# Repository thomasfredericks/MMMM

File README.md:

# MMMM
MMMM: Mini Mono Matrix Mixer

More information: http://www.tofstuff.com/MMMM

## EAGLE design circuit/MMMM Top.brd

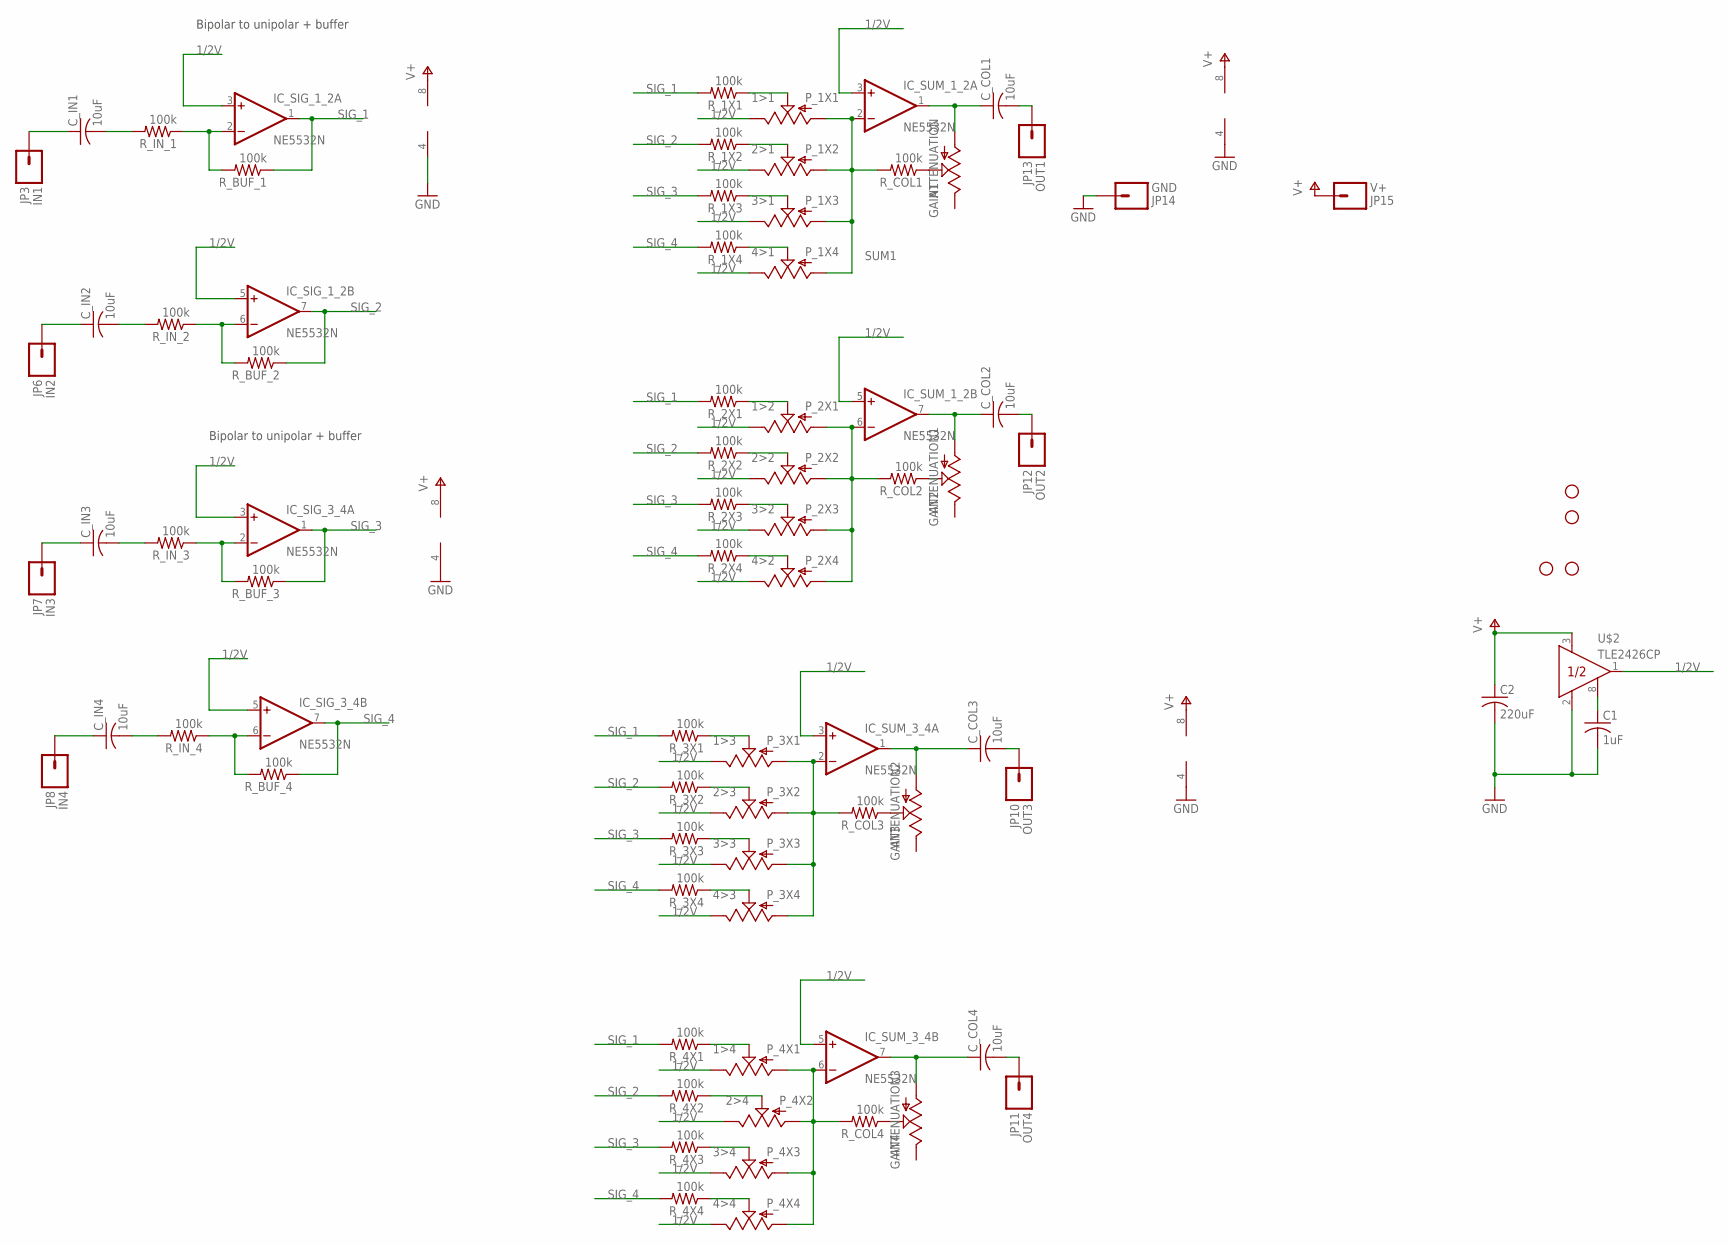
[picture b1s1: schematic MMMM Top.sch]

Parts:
ATTENUATION: GAIN1; TRIM_POT
ATTENUATION1: GAIN2; TRIM_POT
ATTENUATION2: GAIN3; TRIM_POT
ATTENUATION3: GAIN4; TRIM_POT
C1: 1uF; C025-030X050
C2: 220uF; C050-075X075
C_COL1, C_COL2, C_COL3, C_COL4: 10uF; C025-025X050
C_IN1, C_IN2, C_IN3, C_IN4: 10uF; C025-025X050
IC_SIG_1_2, IC_SIG_3_4: NE5532N; DIL08
IC_SUM_1_2, IC_SUM_3_4: NE5532N; DIL08
JP1, JP2, JP4, JP5: STAND-OFF
JP3: IN1; 1X01_SIDE_NAME
JP6: IN2; 1X01_SIDE_NAME
JP7: IN3; 1X01_SIDE_NAME
JP8: IN4; 1X01_SIDE_NAME
JP10: OUT3; 1X01_SIDE_NAME
JP11: OUT4; 1X01_SIDE_NAME
JP12: OUT2; 1X01_SIDE_NAME
JP13: OUT1; 1X01_SIDE_NAME
JP14: GND; 1X01_SIDE_NAME
JP15: V+; 1X01_SIDE_NAME
P_1X1: 1>1; ALPS_POT
P_1X2: 2>1; ALPS_POT
P_1X3: 3>1; ALPS_POT
P_1X4: 4>1; ALPS_POT
P_2X1: 1>2; ALPS_POT
P_2X2: 2>2; ALPS_POT
P_2X3: 3>2; ALPS_POT
P_2X4: 4>2; ALPS_POT
P_3X1: 1>3; ALPS_POT
P_3X2: 2>3; ALPS_POT
P_3X3: 3>3; ALPS_POT
P_3X4: 4>3; ALPS_POT
P_4X1: 1>4; ALPS_POT
P_4X2: 2>4; ALPS_POT
P_4X3: 3>4; ALPS_POT
P_4X4: 4>4; ALPS_POT
R_1X1, R_1X2, R_1X3, R_1X4, R_2X1, R_2X2, R_2X3, R_2X4, R_3X1, R_3X2, R_3X3, R_3X4, R_4X1, R_4X2, R_4X3, R_4X4: 100k; 0204/5
R_BUF_1, R_BUF_2, R_BUF_3, R_BUF_4: 100k; 0204/5
R_COL1, R_COL2, R_COL3, R_COL4: 100k; 0204/5
R_IN_1, R_IN_2, R_IN_3, R_IN_4: 100k; 0204/5
U$2: TLE2426CP; DIP-8

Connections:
1/2V: IC_SIG_1_2.3 (+IN), IC_SIG_1_2.5 (+IN), IC_SIG_3_4.3 (+IN), IC_SIG_3_4.5 (+IN), IC_SUM_1_2.3 (+IN), IC_SUM_1_2.5 (+IN), IC_SUM_3_4.3 (+IN), IC_SUM_3_4.5 (+IN), P_1X1.P$1 (E), P_1X2.P$1 (E), P_1X3.P$1 (E), P_1X4.P$1 (E), P_2X1.P$1 (E), P_2X2.P$1 (E), P_2X3.P$1 (E), P_2X4.P$1 (E), P_3X1.P$1 (E), P_3X2.P$1 (E), P_3X3.P$1 (E), P_3X4.P$1 (E), P_4X1.P$1 (E), P_4X2.P$1 (E), P_4X3.P$1 (E), P_4X4.P$1 (E), U$2.1 (OUT)
GND: C1.2, C2.2, IC_SIG_1_2.4 (V-), IC_SIG_3_4.4 (V-), IC_SUM_1_2.4 (V-), IC_SUM_3_4.4 (V-), JP14.1, U$2.2 (COM)
IN1: C_IN1.1, JP3.1
unnamed: ATTENUATION.1 (S), R_COL1.1
unnamed: IC_SIG_1_2.2 (-IN), R_BUF_1.2, R_IN_1.1
unnamed: C_COL1.2, JP13.1
unnamed: P_2X1.P$2 (S), R_2X1.1
unnamed: ATTENUATION1.1 (S), R_COL2.1
unnamed: C_IN1.2, R_IN_1.2
unnamed: IC_SIG_1_2.6 (-IN), R_BUF_2.2, R_IN_2.1
unnamed: C_IN2.2, R_IN_2.2
unnamed: C_IN2.1, JP6.1
unnamed: P_1X1.P$2 (S), R_1X1.1
unnamed: C1.1, U$2.8 (NR)
unnamed: IC_SIG_3_4.2 (-IN), R_BUF_3.2, R_IN_3.1
unnamed: C_IN3.2, R_IN_3.2
unnamed: C_IN3.1, JP7.1
unnamed: IC_SIG_3_4.6 (-IN), R_BUF_4.2, R_IN_4.1
unnamed: C_IN4.2, R_IN_4.2
unnamed: C_IN4.1, JP8.1
unnamed: ATTENUATION1.3 (A), C_COL2.1, IC_SUM_1_2.7 (OUT)
unnamed: P_1X3.P$2 (S), R_1X3.1
unnamed: P_1X4.P$2 (S), R_1X4.1
unnamed: ATTENUATION.3 (A), C_COL1.1, IC_SUM_1_2.1 (OUT)
unnamed: ATTENUATION2.1 (S), R_COL3.1
unnamed: ATTENUATION3.1 (S), R_COL4.1
unnamed: P_1X2.P$2 (S), R_1X2.1
unnamed: P_2X2.P$2 (S), R_2X2.1
unnamed: C_COL2.2, JP12.1
unnamed: P_2X3.P$2 (S), R_2X3.1
unnamed: IC_SUM_1_2.6 (-IN), P_2X1.P$3 (A), P_2X2.P$3 (A), P_2X3.P$3 (A), P_2X4.P$3 (A), R_COL2.2
unnamed: P_2X4.P$2 (S), R_2X4.1
unnamed: P_3X1.P$2 (S), R_3X1.1
unnamed: ATTENUATION2.3 (A), C_COL3.1, IC_SUM_3_4.1 (OUT)
unnamed: P_3X2.P$2 (S), R_3X2.1
unnamed: C_COL3.2, JP10.1
unnamed: P_3X3.P$2 (S), R_3X3.1
unnamed: IC_SUM_3_4.2 (-IN), P_3X1.P$3 (A), P_3X2.P$3 (A), P_3X3.P$3 (A), P_3X4.P$3 (A), R_COL3.2
unnamed: P_3X4.P$2 (S), R_3X4.1
unnamed: P_4X1.P$2 (S), R_4X1.1
unnamed: ATTENUATION3.3 (A), C_COL4.1, IC_SUM_3_4.7 (OUT)
unnamed: P_4X2.P$2 (S), R_4X2.1
unnamed: C_COL4.2, JP11.1
unnamed: P_4X3.P$2 (S), R_4X3.1
unnamed: IC_SUM_3_4.6 (-IN), P_4X1.P$3 (A), P_4X2.P$3 (A), P_4X3.P$3 (A), P_4X4.P$3 (A), R_COL4.2
unnamed: P_4X4.P$2 (S), R_4X4.1
SIG_1: IC_SIG_1_2.1 (OUT), R_1X1.2, R_2X1.2, R_3X1.2, R_4X1.2, R_BUF_1.1
SIG_2: IC_SIG_1_2.7 (OUT), R_1X2.2, R_2X2.2, R_3X2.2, R_4X2.2, R_BUF_2.1
SIG_3: IC_SIG_3_4.1 (OUT), R_1X3.2, R_2X3.2, R_3X3.2, R_4X3.2, R_BUF_3.1
SIG_4: IC_SIG_3_4.7 (OUT), R_1X4.2, R_2X4.2, R_3X4.2, R_4X4.2, R_BUF_4.1
SUM1: IC_SUM_1_2.2 (-IN), P_1X1.P$3 (A), P_1X2.P$3 (A), P_1X3.P$3 (A), P_1X4.P$3 (A), R_COL1.2
V+: C2.1, IC_SIG_1_2.8 (V+), IC_SIG_3_4.8 (V+), IC_SUM_1_2.8 (V+), IC_SUM_3_4.8 (V+), JP15.1, U$2.3 (IN)

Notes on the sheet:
Bipolar to unipolar + buffer

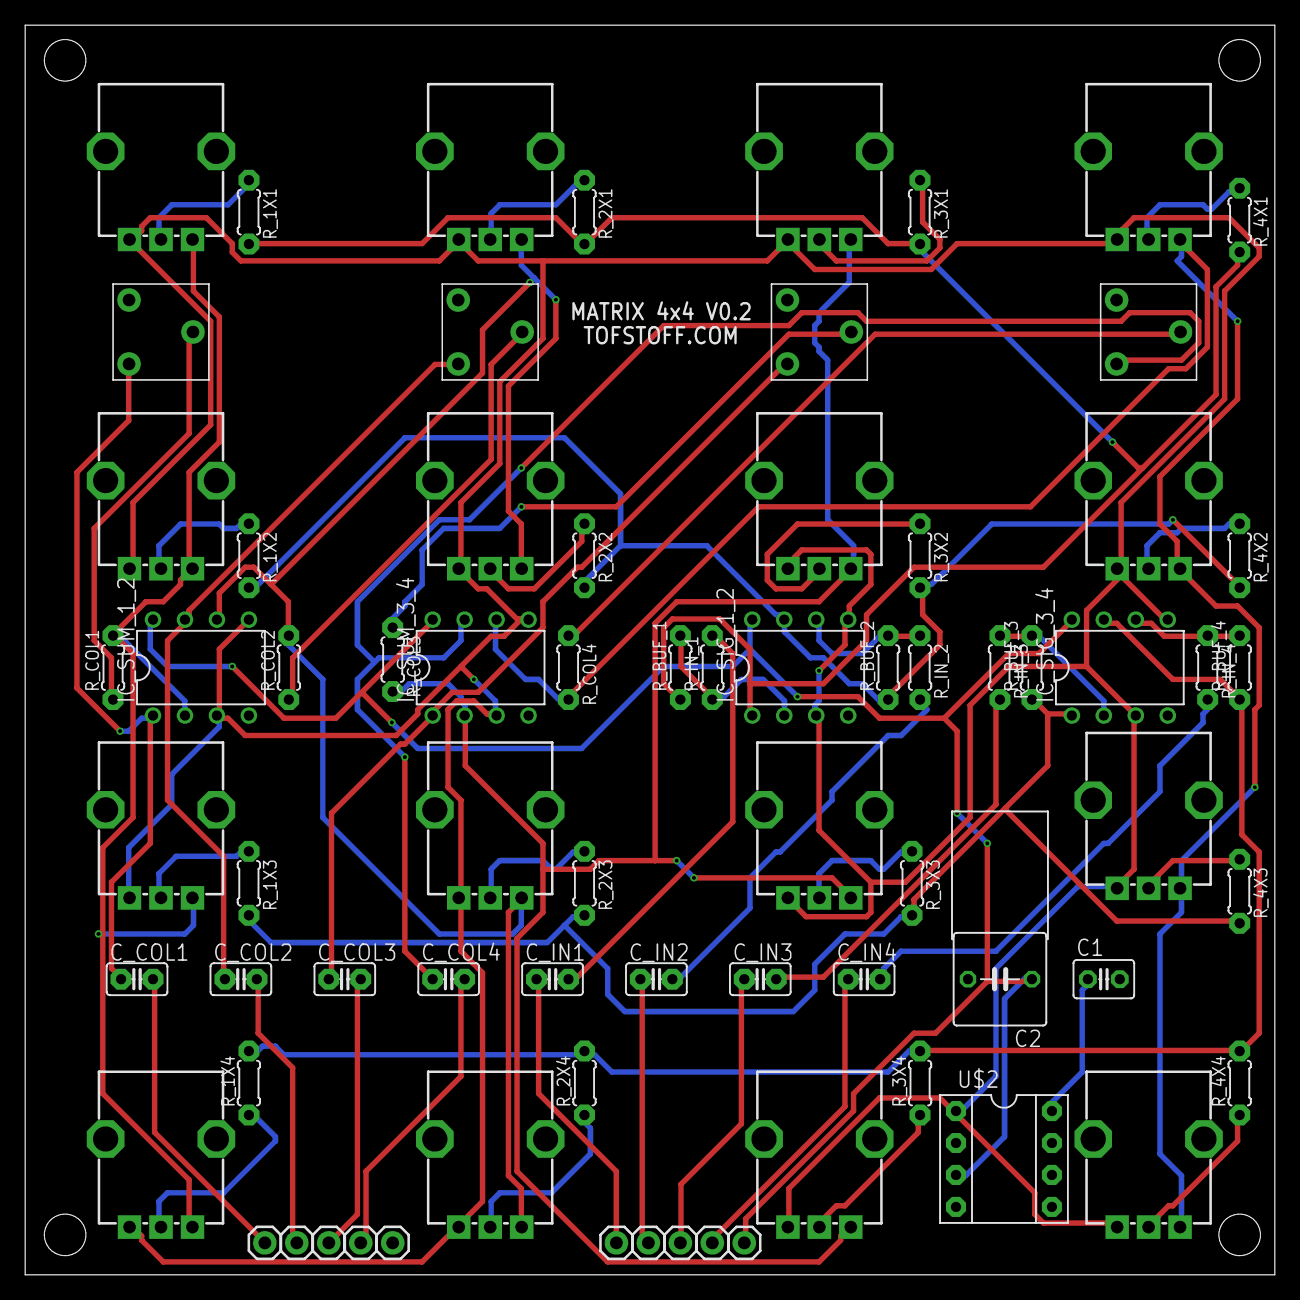
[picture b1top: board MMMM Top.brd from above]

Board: 2 copper layers, 99.3 x 99.3 mm, 77 parts (0 on the bottom side), 52 nets.

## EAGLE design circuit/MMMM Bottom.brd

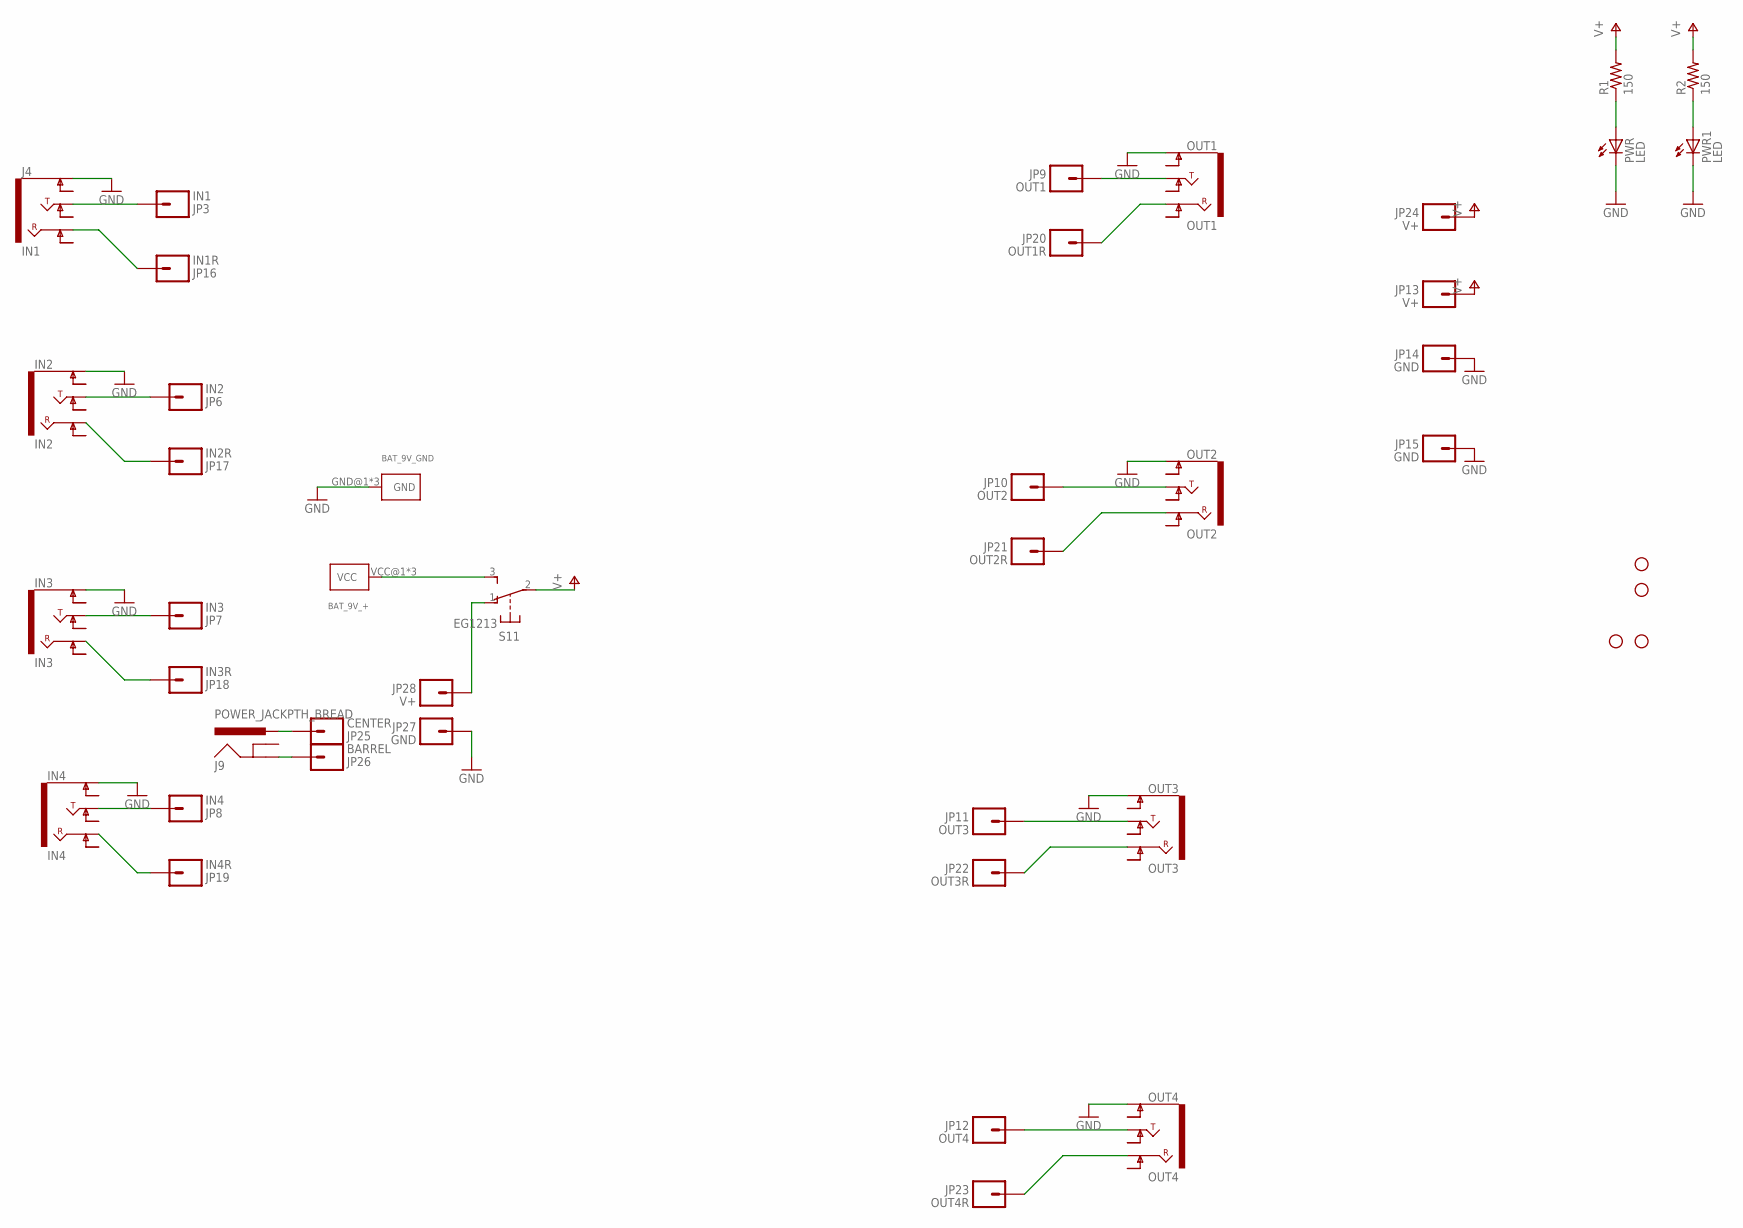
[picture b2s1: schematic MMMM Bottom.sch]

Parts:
BAT_9V_+: KEYSTONE-637; KEYSTONE_AA_AAA_BATTERY_TERMINAL-637
BAT_9V_GND: KEYSTONE-629; KEYSTONE_AA_AAA_BATTERY_TERMINAL-629
IN2: IN2; AUDIO-JACK-.25-INCH-HORIZ-PTH
IN3: IN3; AUDIO-JACK-.25-INCH-HORIZ-PTH
IN4: IN4; AUDIO-JACK-.25-INCH-HORIZ-PTH
J4: IN1; AUDIO-JACK-.25-INCH-HORIZ-PTH
J9: POWER_JACKPTH_BREAD; POWER_JACK_PTH_BREAD
JP1, JP2, JP4, JP5: STAND-OFF
JP3: IN1; 1X01_SIDE_NAME
JP6: IN2; 1X01_SIDE_NAME
JP7: IN3; 1X01_SIDE_NAME
JP8: IN4; 1X01_SIDE_NAME
JP9: OUT1; 1X01_SIDE_NAME
JP10: OUT2; 1X01_SIDE_NAME
JP11: OUT3; 1X01_SIDE_NAME
JP12: OUT4; 1X01_SIDE_NAME
JP13, JP24: V+; 1X01_SIDE_NAME
JP14, JP15: GND; 1X01_SIDE_NAME
JP16: IN1R; 1X01_SIDE_NAME
JP17: IN2R; 1X01_SIDE_NAME
JP18: IN3R; 1X01_SIDE_NAME
JP19: IN4R; 1X01_SIDE_NAME
JP20: OUT1R; 1X01_SIDE_NAME
JP21: OUT2R; 1X01_SIDE_NAME
JP22: OUT3R; 1X01_SIDE_NAME
JP23: OUT4R; 1X01_SIDE_NAME
JP25: CENTER; 1X01_SIDE_NAME_SML
JP26: BARREL; 1X01_SIDE_NAME_SML
JP27: GND; 1X01_SIDE_NAME_SML
JP28: V+; 1X01_SIDE_NAME_SML
OUT1: OUT1; AUDIO-JACK-.25-INCH-HORIZ-PTH
OUT2: OUT2; AUDIO-JACK-.25-INCH-HORIZ-PTH
OUT3: OUT3; AUDIO-JACK-.25-INCH-HORIZ-PTH
OUT4: OUT4; AUDIO-JACK-.25-INCH-HORIZ-PTH
PWR, PWR1: LED; LED3MM-MINUS
R1, R2: 150; 0204/5
S1: EG1213

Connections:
GND: BAT_9V_GND.GND@1, BAT_9V_GND.GND@2, BAT_9V_GND.GND@3, IN2.SLEEVE (EARTH), IN3.SLEEVE (EARTH), IN4.SLEEVE (EARTH), J4.SLEEVE (EARTH), JP14.1, JP15.1, JP27.1, OUT1.SLEEVE (EARTH), OUT2.SLEEVE (EARTH), OUT3.SLEEVE (EARTH), OUT4.SLEEVE (EARTH), PWR.K (C), PWR1.K (C)
unnamed: PWR.A, R1.1
unnamed: IN2.TIP, JP6.1
unnamed: JP9.1, OUT1.TIP
unnamed: IN3.TIP, JP7.1
unnamed: J4.TIP, JP3.1
unnamed: IN4.TIP, JP8.1
unnamed: J4.RING, JP16.1
unnamed: IN3.RING, JP18.1
unnamed: IN4.RING, JP19.1
unnamed: IN2.RING, JP17.1
unnamed: JP20.1, OUT1.RING
unnamed: JP23.1, OUT4.RING
unnamed: JP22.1, OUT3.RING
unnamed: JP21.1, OUT2.RING
unnamed: JP28.1, S1.1 (O)
unnamed: BAT_9V_+.VCC@1, BAT_9V_+.VCC@2, BAT_9V_+.VCC@3, S1.3 (S)
unnamed: PWR1.A, R2.1
unnamed: J9.PWR, JP25.1
unnamed: J9.GND, JP26.1
unnamed: JP10.1, OUT2.TIP
unnamed: JP11.1, OUT3.TIP
unnamed: JP12.1, OUT4.TIP
V+: JP13.1, JP24.1, R1.2, R2.2, S1.2

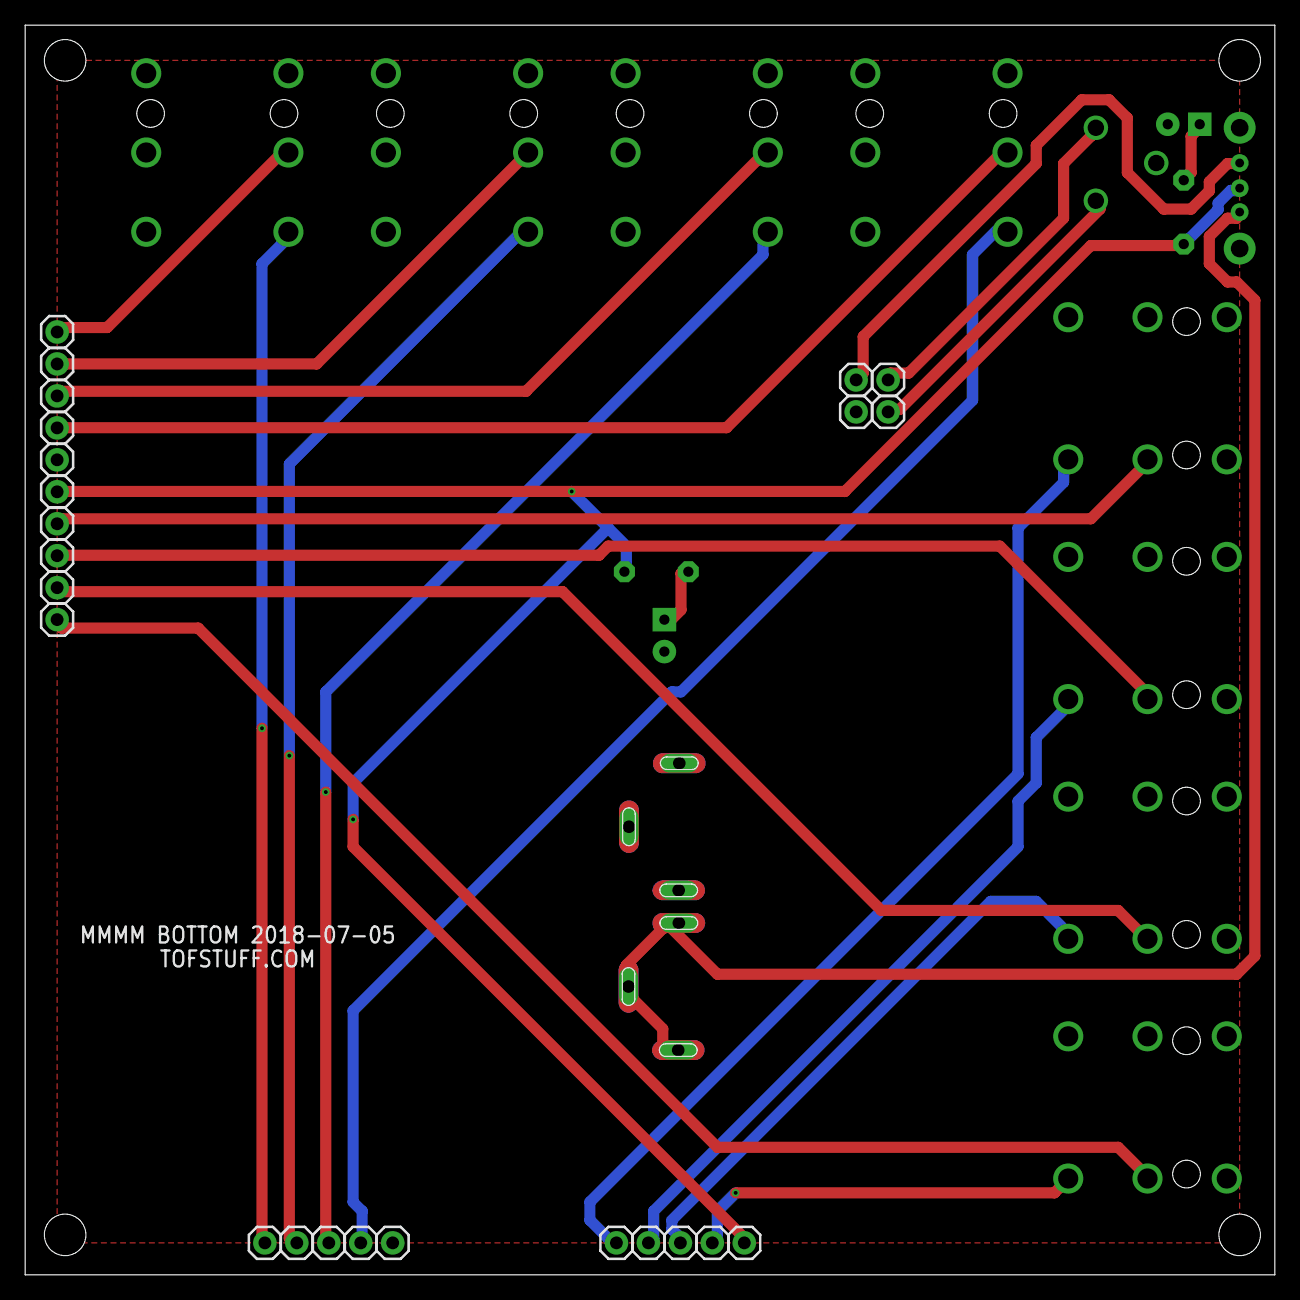
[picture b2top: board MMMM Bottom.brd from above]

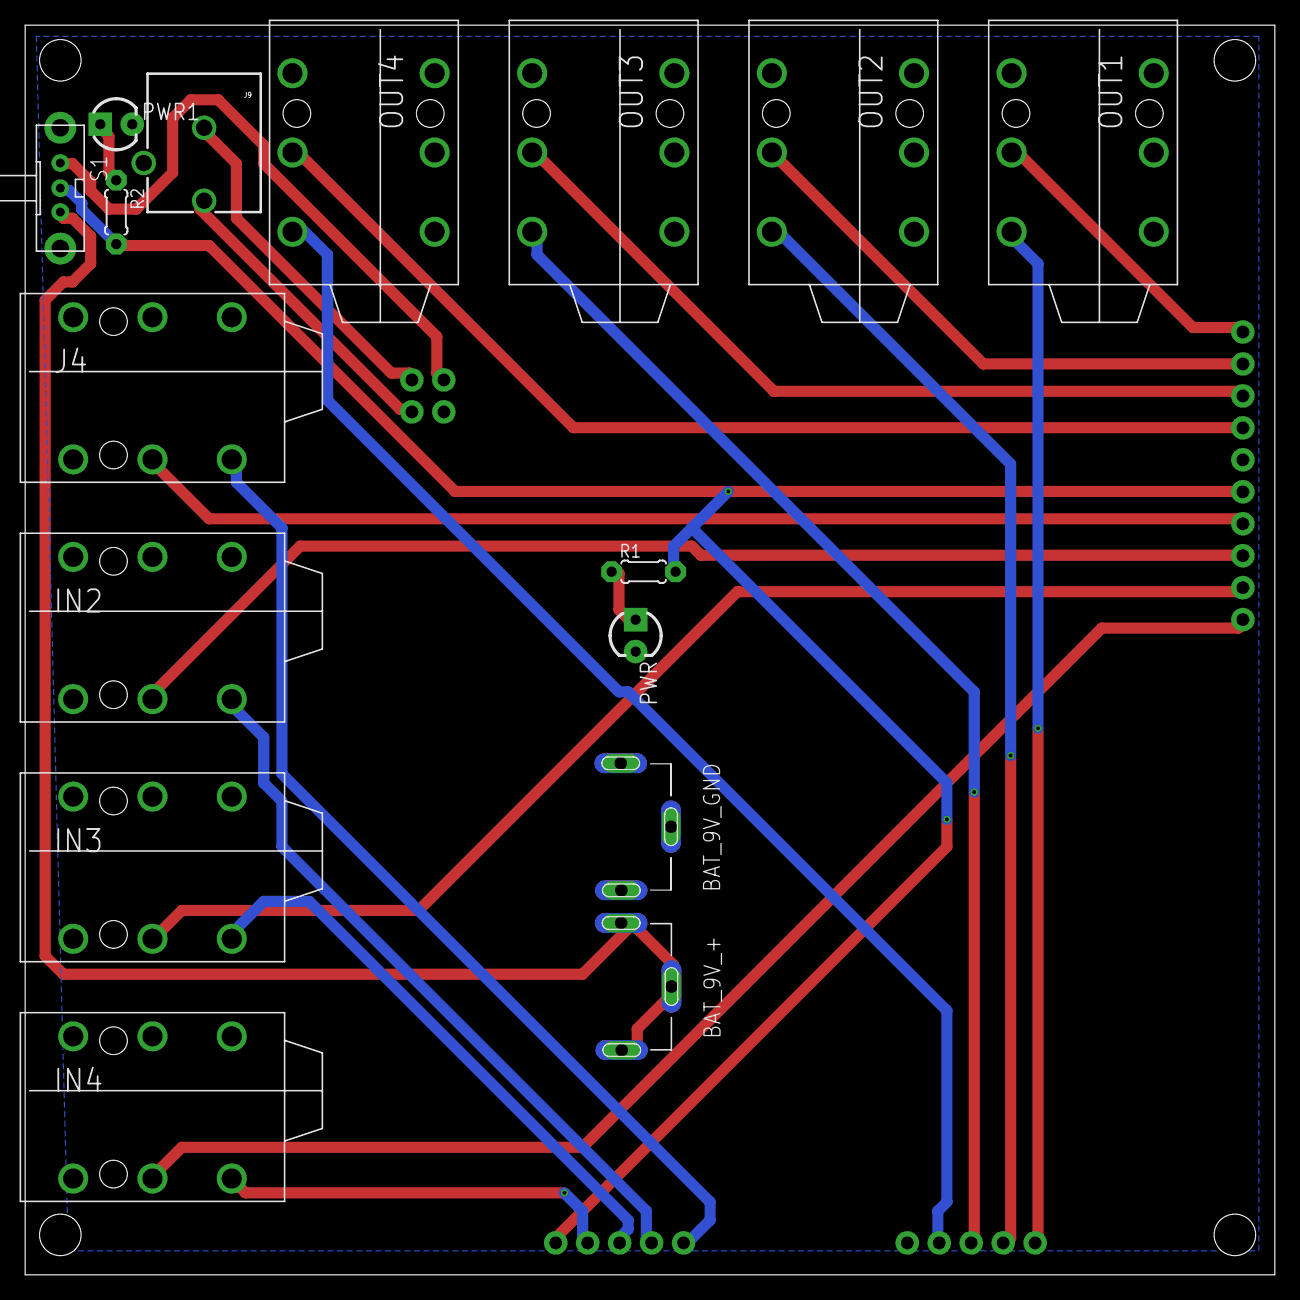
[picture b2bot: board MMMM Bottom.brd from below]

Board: 2 copper layers, 99.2 x 99.2 mm, 44 parts (16 on the bottom side), 24 nets.

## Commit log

2018-05-22 Added circuits

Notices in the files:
parts and their libraries:
SparkFun-Connectors: Licensing: Creative Commons ShareAlike 4.0 International - https://creativecommons.org/licenses/by-sa/4.0
